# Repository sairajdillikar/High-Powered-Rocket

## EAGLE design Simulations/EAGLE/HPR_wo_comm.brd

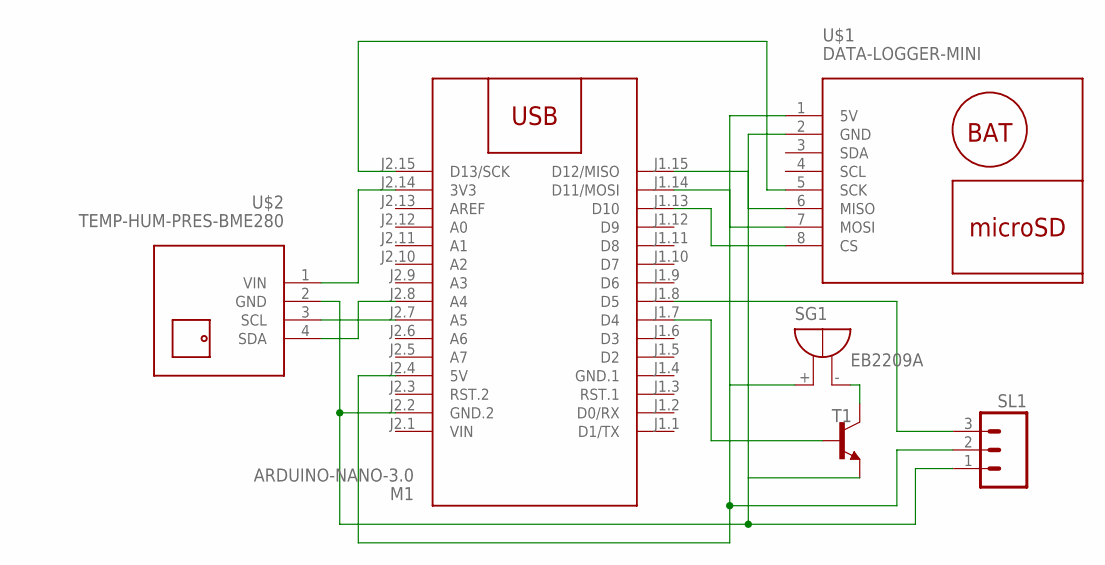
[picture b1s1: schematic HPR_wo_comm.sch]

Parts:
M1: ARDUINO-NANO-3.0
SG1: EB2209A
SL1: M03; 03P
T1: 2N3700-NPN-TO18-EBC; TO18
U$1: DATA-LOGGER-MINI
U$2: TEMP-HUM-PRES-BME280

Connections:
GND.1: M1.J1.4 (GND.1)
unnamed: M1.J2.14 (3V3), U$2.1 (VIN)
unnamed: M1.J1.7 (D4), T1.2 (B)
unnamed: M1.J2.7 (A5), U$2.3 (SCL)
unnamed: M1.J2.8 (A4), U$2.4 (SDA)
unnamed: M1.J1.15 (D12/MISO), U$1.6 (MISO)
unnamed: M1.J1.14 (D11/MOSI), U$1.7 (MOSI)
unnamed: M1.J1.13 (D10), U$1.8 (CS)
unnamed: M1.J2.15 (D13/SCK), U$1.5 (SCK)
unnamed: M1.J2.4 (5V), SG1.+, SL1.2, U$1.1 (5V)
unnamed: M1.J2.2 (GND.2), SL1.1, T1.1 (E), U$1.2 (GND), U$2.2 (GND)
unnamed: SG1.-, T1.3 (C)
unnamed: M1.J1.8 (D5), SL1.3
VIN: M1.J2.1 (VIN)

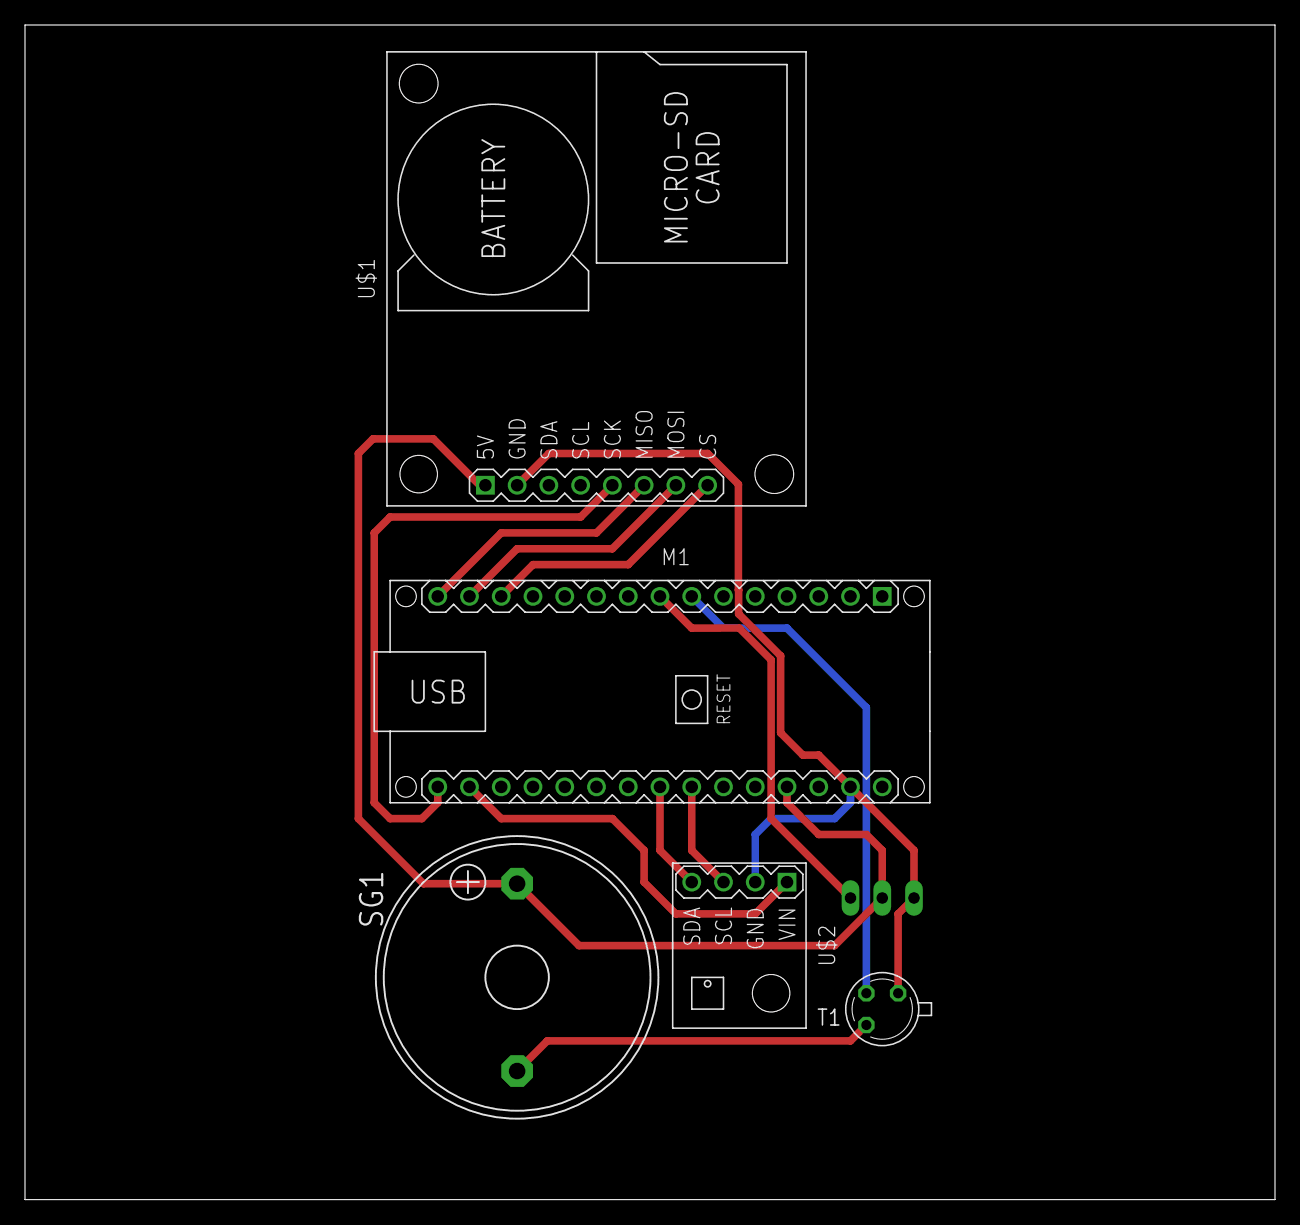
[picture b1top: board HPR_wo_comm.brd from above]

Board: 2 copper layers, 100.0 x 94.0 mm, 6 parts (1 on the bottom side), 12 nets.

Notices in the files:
parts and their libraries:
diy-modules: Released under the Creative Commons Attribution 4.0 International License: http://creativecommons.org/licenses/by/4.0
